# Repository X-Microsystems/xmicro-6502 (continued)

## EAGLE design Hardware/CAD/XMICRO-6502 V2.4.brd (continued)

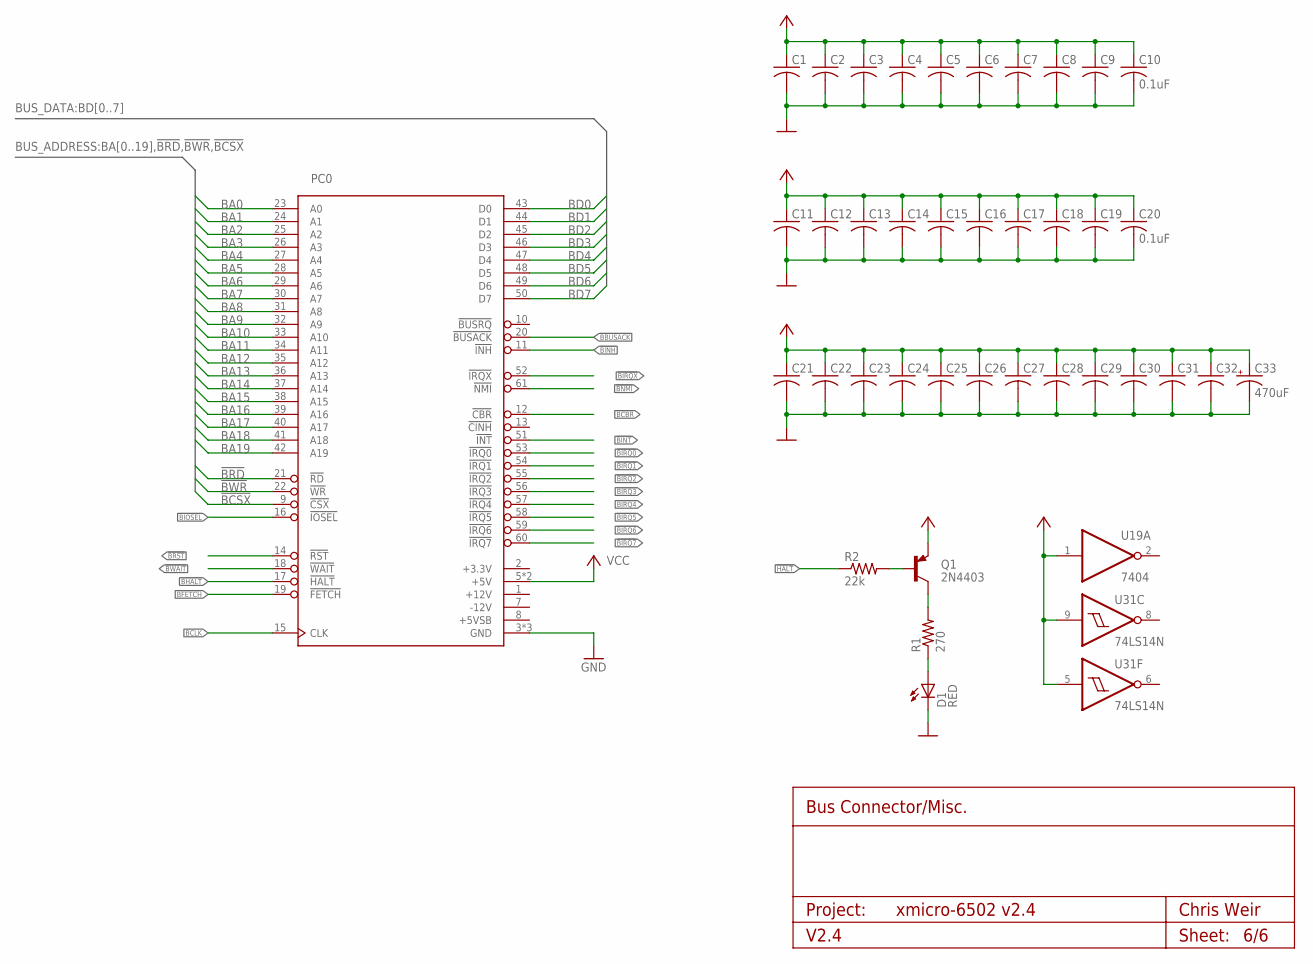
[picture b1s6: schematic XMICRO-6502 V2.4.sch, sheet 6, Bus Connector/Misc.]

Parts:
C1, C2, C3, C4, C5, C6, C7, C8, C9, C10, C11, C12, C13, C14, C15, C16, C17, C18, C19, C20, C21, C22, C23, C24, C25, C26, C27, C28, C29, C30, C31, C32: 0.1uF; C025-024X044
C33: 470uF; C-10-5
D1: RED; LED5MM
PC0: XMICRO-BUS-EDGE62M; EDGE62M
Q1: 2N4403; TO92
R1: 270; 0207/10
R2: 22k; 0207/10
U19: 7404; DIL14
U31: 74LS14N; DIL14

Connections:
!BBUSACK: PC0.20 (!BUSACK); also elsewhere on the board
!BCBR: PC0.12 (!CBR); also elsewhere on the board
!BCSX: PC0.9 (!CSX); also elsewhere on the board
!BFETCH: PC0.19 (!FETCH); also elsewhere on the board
!BHALT: PC0.17 (!HALT); also elsewhere on the board
!BINH: PC0.11 (!INH); also elsewhere on the board
!BINT: PC0.51 (!INT); also elsewhere on the board
!BIOSEL: PC0.16 (!IOSEL); also elsewhere on the board
!BIRQ0: PC0.53 (!IRQ0); also elsewhere on the board
!BIRQ1: PC0.54 (!IRQ1); also elsewhere on the board
!BIRQ2: PC0.55 (!IRQ2); also elsewhere on the board
!BIRQ3: PC0.56 (!IRQ3); also elsewhere on the board
!BIRQ4: PC0.57 (!IRQ4); also elsewhere on the board
!BIRQ5: PC0.58 (!IRQ5); also elsewhere on the board
!BIRQ6: PC0.59 (!IRQ6); also elsewhere on the board
!BIRQ7: PC0.60 (!IRQ7); also elsewhere on the board
!BIRQX: PC0.52 (!IRQX); also elsewhere on the board
!BNMI: PC0.61 (!NMI); also elsewhere on the board
!BRD: PC0.21 (!RD); also elsewhere on the board
!BRST: PC0.14 (!RST); also elsewhere on the board
!BWAIT: PC0.18 (!WAIT); also elsewhere on the board
!BWR: PC0.22 (!WR); also elsewhere on the board
!HALT: R2.1; also elsewhere on the board
BA0: PC0.23 (A0); also elsewhere on the board
BA1: PC0.24 (A1); also elsewhere on the board
BA2: PC0.25 (A2); also elsewhere on the board
BA3: PC0.26 (A3); also elsewhere on the board
BA4: PC0.27 (A4); also elsewhere on the board
BA5: PC0.28 (A5); also elsewhere on the board
BA6: PC0.29 (A6); also elsewhere on the board
BA7: PC0.30 (A7); also elsewhere on the board
BA8: PC0.31 (A8); also elsewhere on the board
BA9: PC0.32 (A9); also elsewhere on the board
BA10: PC0.33 (A10); also elsewhere on the board
BA11: PC0.34 (A11); also elsewhere on the board
BA12: PC0.35 (A12); also elsewhere on the board
BA13: PC0.36 (A13); also elsewhere on the board
BA14: PC0.37 (A14); also elsewhere on the board
BA15: PC0.38 (A15); also elsewhere on the board
BA16: PC0.39 (A16); also elsewhere on the board
BA17: PC0.40 (A17); also elsewhere on the board
BA18: PC0.41 (A18); also elsewhere on the board
BA19: PC0.42 (A19); also elsewhere on the board
BCLK: PC0.15 (CLK); also elsewhere on the board
BD0: PC0.43 (D0); also elsewhere on the board
BD1: PC0.44 (D1); also elsewhere on the board
BD2: PC0.45 (D2); also elsewhere on the board
BD3: PC0.46 (D3); also elsewhere on the board
BD4: PC0.47 (D4); also elsewhere on the board
BD5: PC0.48 (D5); also elsewhere on the board
BD6: PC0.49 (D6); also elsewhere on the board
BD7: PC0.50 (D7); also elsewhere on the board
GND: C1.2, C2.2, C3.2, C4.2, C5.2, C6.2, C7.2, C8.2, C9.2, C10.2, C11.2, C12.2, C13.2, C14.2, C15.2, C16.2, C17.2, C18.2, C19.2, C20.2, C21.2, C22.2, C23.2, C24.2, C25.2, C26.2, C27.2, C28.2, C29.2, C30.2, C31.2, C32.2, C33.-, D1.K (C), PC0.3 (GND), PC0.4 (GND), PC0.62 (GND), U19.7 (GND), U31.7 (GND); also elsewhere on the board
unnamed: Q1.2 (B), R2.2
unnamed: Q1.3 (C), R1.2
unnamed: D1.A, R1.1
VCC: C1.1, C2.1, C3.1, C4.1, C5.1, C6.1, C7.1, C8.1, C9.1, C10.1, C11.1, C12.1, C13.1, C14.1, C15.1, C16.1, C17.1, C18.1, C19.1, C20.1, C21.1, C22.1, C23.1, C24.1, C25.1, C26.1, C27.1, C28.1, C29.1, C30.1, C31.1, C32.1, C33.+, PC0.5 (+5V), PC0.6 (+5V), Q1.1 (E), U19.1 (I), U19.14 (VCC), U31.5 (I), U31.9 (I), U31.14 (VCC); also elsewhere on the board

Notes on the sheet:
Bus Connector/Misc.
Project:
V2.4
Chris Weir
Sheet:

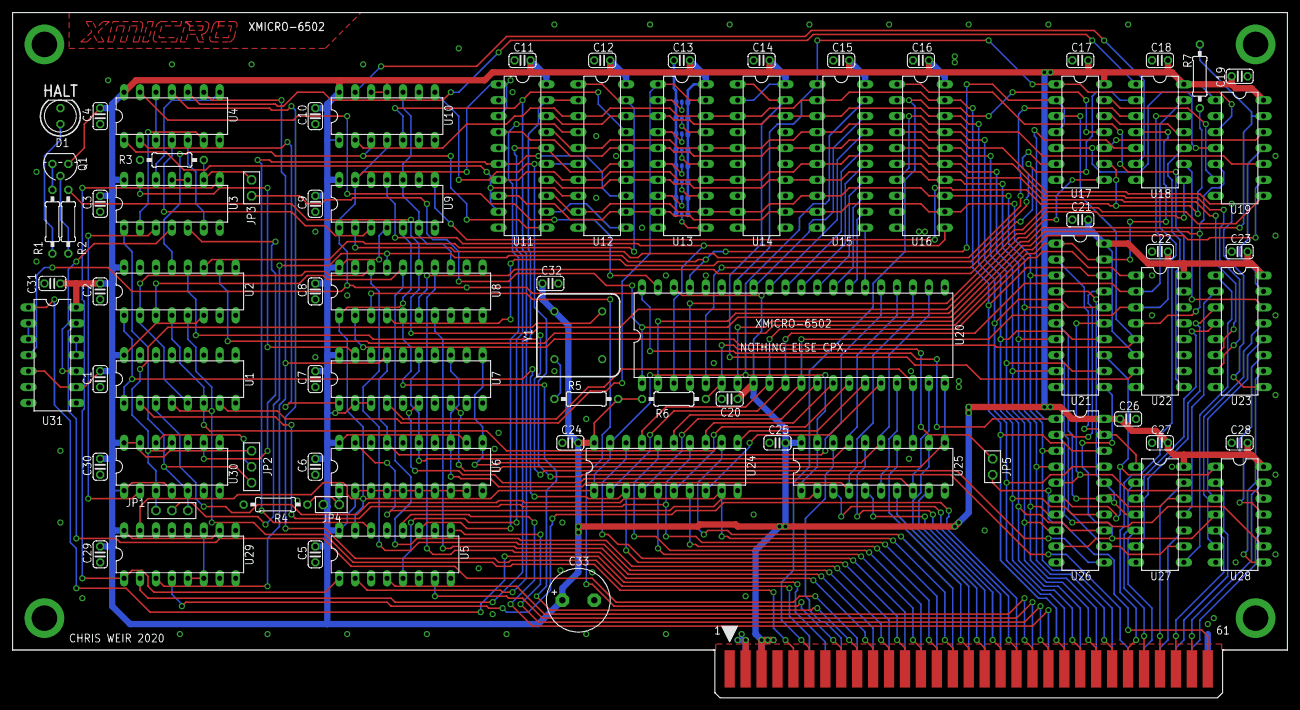
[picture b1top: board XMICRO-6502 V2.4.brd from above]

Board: 2 copper layers, 203.2 x 109.2 mm, 80 parts (0 on the bottom side), 163 nets.

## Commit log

2018-08-16 Updated the name in the license
2019-03-24 Rearranged hardware directory
2019-03-24 Removed CAD/CAM from documentation directory
2019-03-24 Added documentation for hardware V2
2019-05-28 Updated schematic xrefs to indicate signal direction.
2019-12-09 Updated to V2.3. Fixed wait states.
2020-03-30 Updated to V2.4 - made it necessary to manually clear DMA interrupts
2020-08-30 Added picture and updated README.md
2025-08-05 Updated Readme and photos
